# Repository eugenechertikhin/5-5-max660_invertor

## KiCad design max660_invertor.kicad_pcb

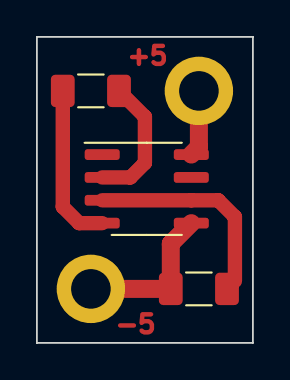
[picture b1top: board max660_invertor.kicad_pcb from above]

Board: 2 copper layers, 12.0 x 17.0 mm, 5 parts (0 on the bottom side), 5 nets.

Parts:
C1, C2: 150uF; C_1206_3216Metric_Pad1.33x1.80mm_HandSolder
H1, H2: MountingHole_2.2mm_M2_DIN965_Pad
U1: MAX660; SOIC-8_3.9x4.9mm_P1.27mm

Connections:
+5V: H2.1, U1.8 (VIN)
-5V: C2.2, H1.1, U1.5 (SHDN)
GND: C2.1, U1.3 (VOUT1), U1.6 (VSET)
unnamed: C1.2, U1.4 (GND)
unnamed: C1.1, U1.2 (VOUT2)

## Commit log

2024-03-29 setup repo
2024-03-29 final
2024-09-02 add image
2024-09-04 add labels
